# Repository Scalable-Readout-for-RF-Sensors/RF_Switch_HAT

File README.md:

# RF_Switch_HAT
PCB Design for the RF_Switch_HAT

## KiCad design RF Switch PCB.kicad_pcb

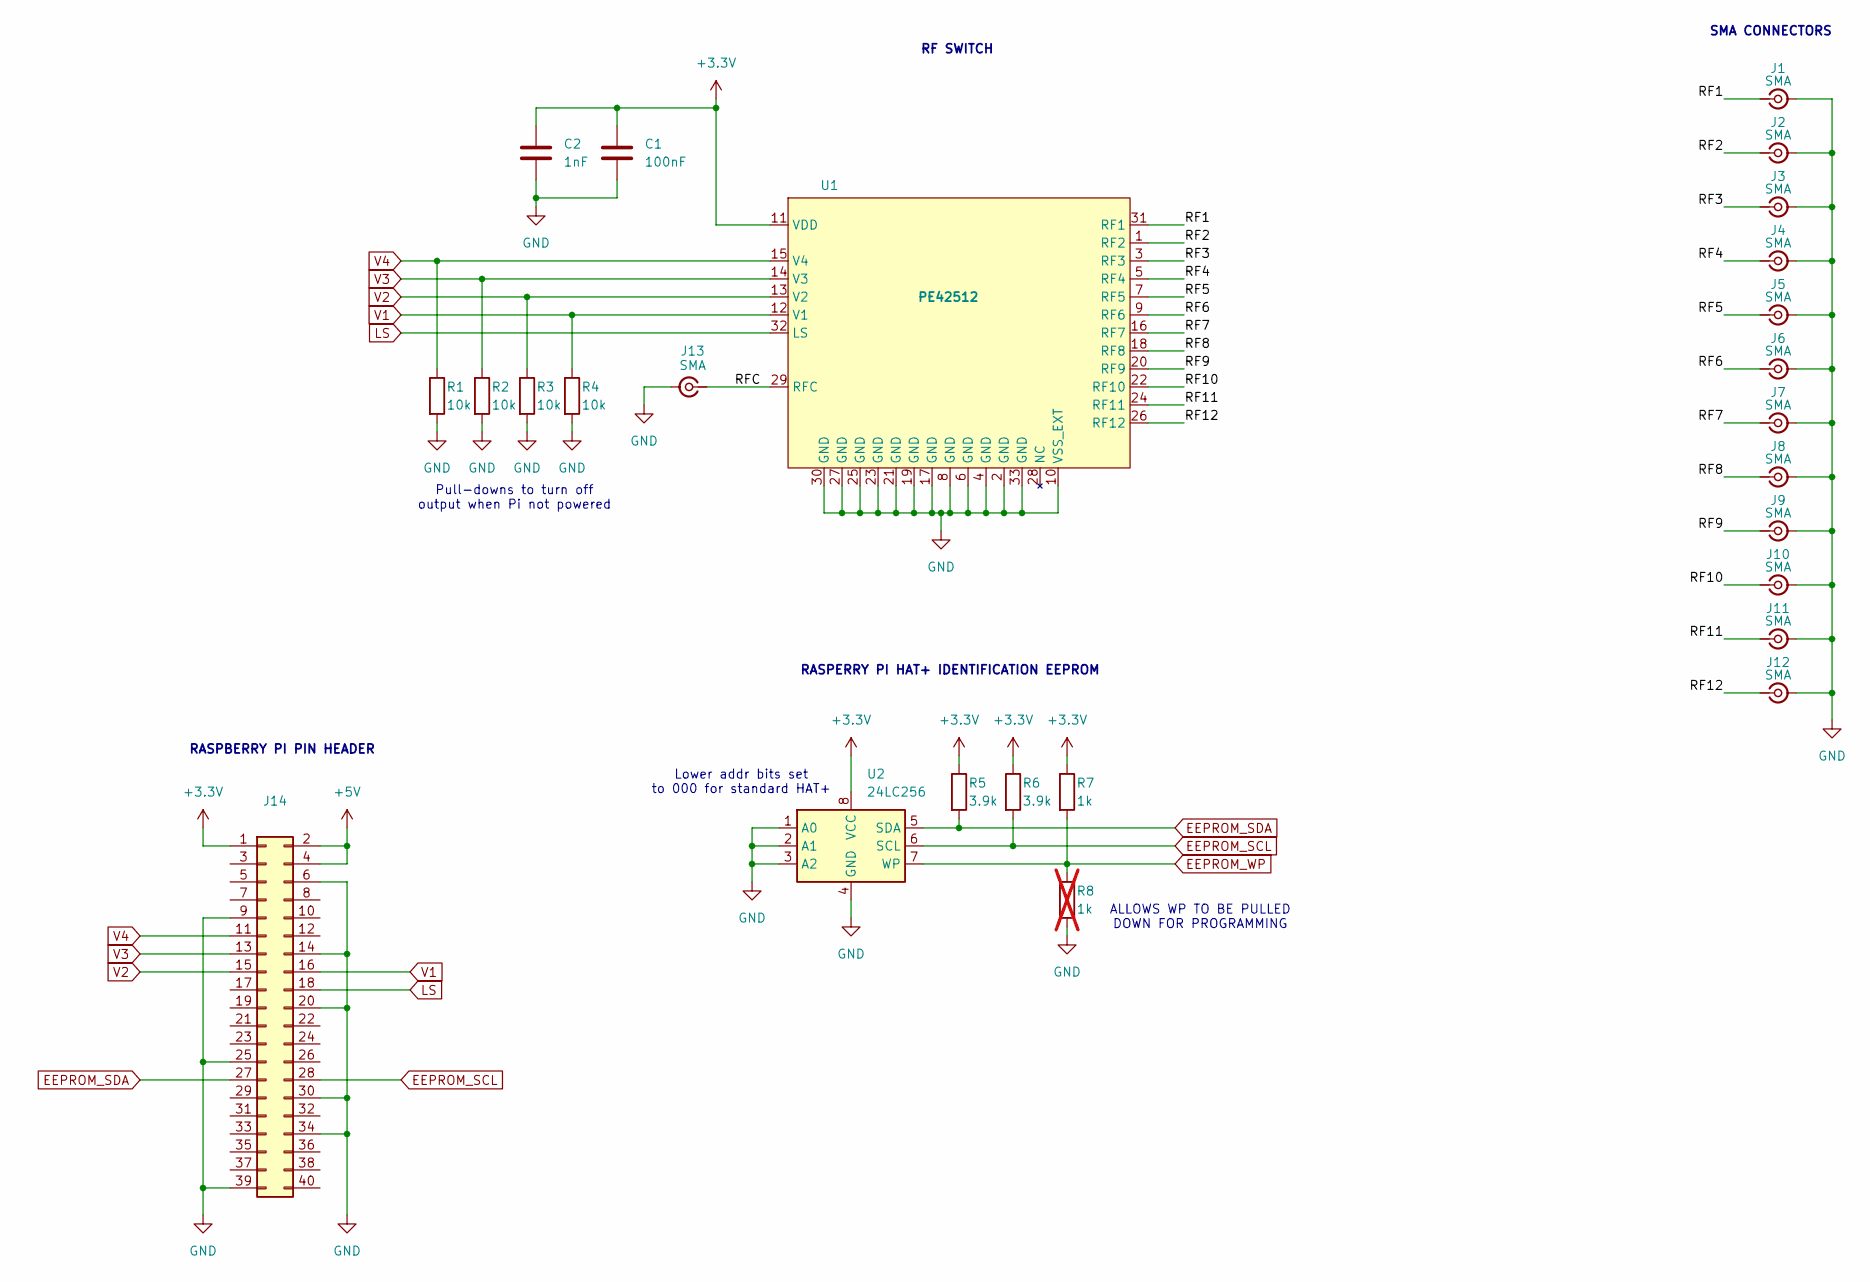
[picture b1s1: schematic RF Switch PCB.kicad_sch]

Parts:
C1: 100nF; C_0805_2012Metric
C2: 1nF; C_0805_2012Metric
J1, J2, J3, J4, J5, J6, J7, J8, J9, J10, J11, J12, J13: SMA; SMA_Amphenol_132289_EdgeMount
J14: Conn_02x20_Odd_Even; PinSocket_2x20_P2.54mm_Vertical
R1, R2, R3, R4: 10k; R_0805_2012Metric
R5, R6: 3.9k; R_0805_2012Metric
R7: 1k; R_0805_2012Metric
R8: 1k; R_0805_2012Metric; not fitted
U1: PE42512; QFN-32-1EP_5x5mm_P0.5mm_EP3.1x3.1mm
U2: 24LC256; DIP-8_W7.62mm

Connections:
+3.3V: C1.1, C2.1, J14.1, R5.1, R6.1, R7.1, U1.11 (VDD), U2.8 (VCC)
+5V: J14.2, J14.4
/RF1: J1.1 (In), U1.31 (RF1)
/RF2: J2.1 (In), U1.1 (RF2)
/RF3: J3.1 (In), U1.3 (RF3)
/RF4: J4.1 (In), U1.5 (RF4)
/RF5: J5.1 (In), U1.7 (RF5)
/RF6: J6.1 (In), U1.9 (RF6)
/RF7: J7.1 (In), U1.16 (RF7)
/RF8: J8.1 (In), U1.18 (RF8)
/RF9: J9.1 (In), U1.20 (RF9)
/RF10: J10.1 (In), U1.22 (RF10)
/RF11: J11.1 (In), U1.24 (RF11)
/RF12: J12.1 (In), U1.26 (RF12)
/RFC: J13.1 (In), U1.29 (RFC)
EEPROM_SCL: J14.28, R6.2, U2.6 (SCL)
EEPROM_SDA: J14.27, R5.2, U2.5 (SDA)
EEPROM_WP: R7.2, R8.1, U2.7 (WP)
GND: C1.2, C2.2, J1.2 (Ext), J2.2 (Ext), J3.2 (Ext), J4.2 (Ext), J5.2 (Ext), J6.2 (Ext), J7.2 (Ext), J8.2 (Ext), J9.2 (Ext), J10.2 (Ext), J11.2 (Ext), J12.2 (Ext), J13.2 (Ext), J14.6, J14.9, J14.14, J14.20, J14.25, J14.30, J14.34, J14.39, R1.2, R2.2, R3.2, R4.2, R8.2, U1.2 (GND), U1.4 (GND), U1.6 (GND), U1.8 (GND), U1.10 (VSS_EXT), U1.17 (GND), U1.19 (GND), U1.21 (GND), U1.23 (GND), U1.25 (GND), U1.27 (GND), U1.30 (GND), U1.33 (GND), U2.1 (A0), U2.2 (A1), U2.3 (A2), U2.4 (GND)
LS: J14.18, U1.32 (LS)
V1: J14.16, R4.1, U1.12 (V1)
V2: J14.15, R3.1, U1.13 (V2)
V3: J14.13, R2.1, U1.14 (V3)
V4: J14.11, R1.1, U1.15 (V4)

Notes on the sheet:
ALLOWS WP TO BE PULLED DOWN FOR PROGRAMMING
RASPERRY PI HAT+ IDENTIFICATION EEPROM
Lower addr bits set to 000 for standard HAT+
SMA CONNECTORS
RF SWITCH
Pull-downs to turn off output when Pi not powered
RASPBERRY PI PIN HEADER

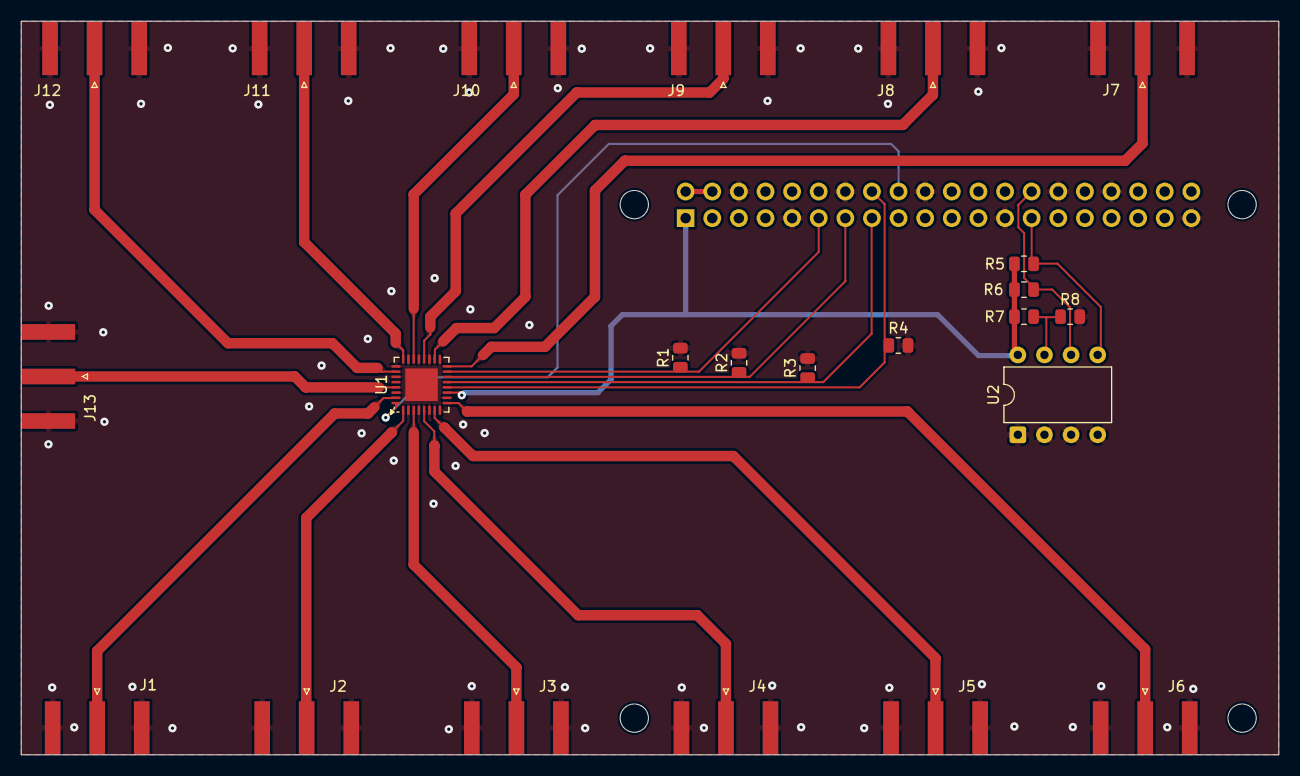
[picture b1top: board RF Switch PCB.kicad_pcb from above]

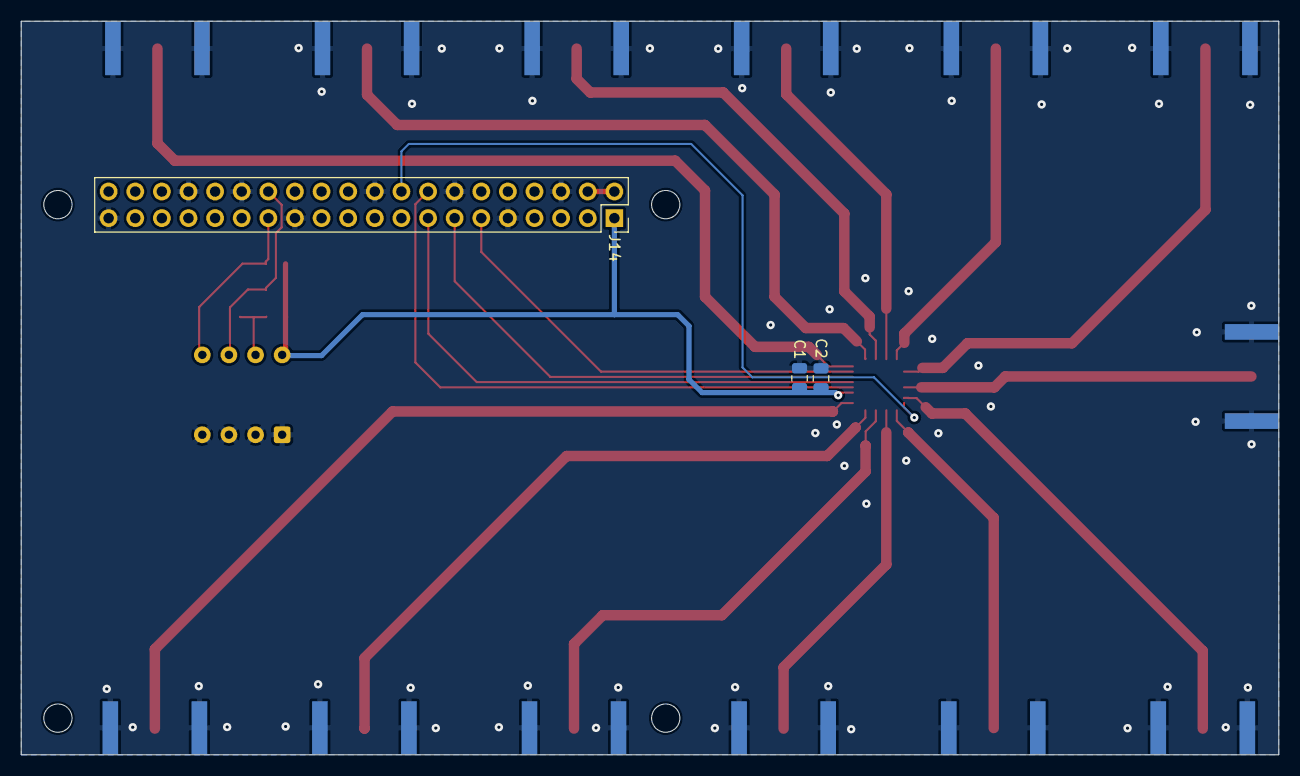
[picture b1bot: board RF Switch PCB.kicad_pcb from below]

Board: 2 copper layers, 120.0 x 70.0 mm, 26 parts (3 on the bottom side), 24 nets.

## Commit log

2025-03-26 Hardware first draft
    Added schematic and initial PCB layout
